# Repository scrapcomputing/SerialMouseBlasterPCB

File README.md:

# Serial Mouse Blaster (a.k.a. Passive USB to Serial Mouse Adapter)

A PCB used for modding a modern optical USB mouse and converting it into a Serial mouse.

This is based on a Raspberry Pi Pico running the SerialMouseBlaster [firmware](https://github.com/scrapcomputing/SerialMouseBlasterFirmware).

# What does it do

The SerialMouseBlaster has two jobs:
- It extracts as much current as possible from the serial port pins and provides power to a Raspberry Pi Pico running the specifically designed low-power firmware, and to a USB optical mouse with the LED resistor mod for low power consumption.
- It does the necessary level shifting that allows the Pico's GPIOs to talk to the serial port pins that are used by the serial mouse protocol.

The end result is an adapter board that converts a USB optical mouse to a serial one with no external power.

# Which mouse can I use?

Short answer: You have to measure it first, but a relatively modern mouse with a < 5mA consumption on idle should work after the resistor mod.

The serial port provides very little power, up to 15mA in total at 5V.
Currently the Pico consumes about half of it and the rest of the circuitry about another 15-20%. So the we only have about 5mA to spare for the USB mouse. So a good mouse candidate is one that consumes up to 5mA.

The problem though is that most USB optical mice consume much more than this.
But most of the power is usually consumed by the LED (usually red) which illuminates the surface.
Luckily the mouse camera can still work even with a much dimmer LED.
So we can reduce the power consumption by adding a resistor in series with the LED.
A good resistor values is usually around 1K Ohms.
Some mice may even work with higher resistor values, but beyond some value the camera can no longer see the surface and the mouse will not register mouse movement.
So for best results use the largest resistor value you can without affecting the functionality of the mouse.

Some mice already have an SMD resistor in-series with the LED (see image below of the Microsoft Basic Optical Mouse v2.0).
This resistor is usually a very low value.
For a cleaner mod, you can simply replace this resistor with another SMD one of much higher value.

You can usually tell if a mouse is low-power enough by simply measuring its idle current, without the resistor mod.
If it is under 5mA, then it has a good chance of working well with a mod.
If not, then the chances are that it will consume too much power even with the mod.

Please note that a typical optical USB mouse will consume several times higher power when you move it as the LED becomes a lot brighter than when it is not moving.

## List of mice that work:
 Brand     |  Model                  | Idle Current | Max Current | Mod Resistor |Modded Idle | Modded Max
-----------|-------------------------|--------------|-------------|--------------|------------|-----------
Microsoft  |Basic Optical Mouse v2.0 | 3.5mA        | ~15mA       |  2.2K        | 2.7mA      | 5.4mA
Logitech   | B100                    | 8.4mA        | ~24mA       |  1K          | 6.4mA      | 8.6mA

## List of mice that consume too much power (mostly very early optical mice):
 Brand     |  Model                   | Idle Current | Max Current |
-----------|--------------------------|--------------|-------------|
Dell       | M-UVDEL1                 | 20.7mA       | 59.2mA      |
Apple      | A1152                    | 26.7mA       | 69.7mA      |
Microsoft  | Basic Optical Mouse      | 29.4mA       | 54.3mA      |
Microsoft  | Wheel Mouse Optical 1.1A | 44.1mA       | 61.4mA      |

> **Note**
> Please help me populate these tables. Feel free to reach out or send out a pull request if you measured your mouse and you want to share your numbers.

# How does it work

The serial port does not provide power.
So any device connected to it either needs to be powered externally, or try to use power from the logic output pins. There are 3 output pins: TXD, DTR and RTS. These can usually provide up to about 5mA at 5V.

The SerialMouseBlaster uses power from all three pins. When the mouse driver initializes the serial port, DTR and RTS are high (about +10V), while TXD is low (about -10V). In order to get power from TXD, it uses a 7555 timer chip as a voltage doubler, which outputs positive voltage.

Level-shifting is done with an LM385 Op Amp which consumes only 1.5mA, as opposed to using a MAX3232, which according to my measurements consumed more than 5mA.

# Serial port pinout

Pin | Name | Direction | Description
----|------|-----------|------------
  1 | CD   | IN        | Carrier Detect
  2 | RXD  | IN        | Receive Data
  3 | TXD  | OUT       | Transmit Data
  4 | DTR  | OUT       | Data Terminal Ready
  5 | GND  |           | Ground
  6 | DSR  | IN        | Data Set Ready
  7 | RTS  | OUT       | Request To Send
  8 | CTS  | IN        | Clear To Send
  9 | IR   | IN        | Ring Indicator

```
Female connector looking at the holes:
 -----------------------
|     -------------     |
|     \ 5 4 3 2 1 /     |
| ( )  \ 9 8 7 6 /  ( ) |
|        -------        |
 -----------------------
```

# Videos
- For a discussion/explanation of the circuit: https://www.youtube.com/watch?v=cGvVPzlRPjM
- Assembly video rev0.1: https://www.youtube.com/watch?v=YjD63UplQ3c

# Bill of materials

Gerber files are published in the releases: https://github.com/scrapcomputing/SerialMouseBlasterPCB/releases

The firmware is available here: https://github.com/scrapcomputing/SerialMouseBlasterFirmware

Reference| Quantity| Value| Footprint | Details
---------|---------|------|-----------|--------
C1 C7 |2|1uF|Capacitor SMD|C 1206 3216Metric Pad1.33x1.80mm
C2 |1|10nF|Capacitor SMD|C 1206 3216Metric Pad1.33x1.80mm
C3 C4 C6 C8 |4|10uF|Capacitor SMD|C 1206 3216Metric Pad1.33x1.80mm
D11 |1|BZX84-C5V1|Diode SMD|D SOT-23 ANK
D1 D2 D3 D4 D5 D6 |6|BAS40-04|Package TO SOT SMD|SOT-23
J1 |1|Conn 01x05|Connector PinHeader 2.54mm|PinHeader 1x05 P2.54mm Vertical
J2 |1|Conn 01x04 Male|Connector PinHeader 2.54mm|PinHeader 1x04 P2.54mm Vertical
J3 |1|Conn 01x03 Male|Connector PinHeader 2.54mm|PinHeader 1x03 P2.54mm Vertical
Q1 |1|MMBTA92|Package TO SOT SMD|SOT-23
R1 R3 R4 R8 |4|1K|Resistor SMD|R 1206 3216Metric Pad1.30x1.75mm
R2 R5 R6 R7 |4|22K|Resistor SMD|R 1206 3216Metric Pad1.30x1.75mm
U1 |1|ICM7555xP|Package SO|SO-8 5.3x6.2mm P1.27mm
U2 |1|LM358|Package SO|SO-8 5.3x6.2mm P1.27mm
U3 |1|RaspberryPi Pico| N/A | Raspberry Pi Pico

# Changelist
- Rev0.4 : Handles Tx with positive voltage, adds protection diode for 555.
- Rev0.3 : First SMD only revision.
- Rev0.2 : Initial release. Fixes minor issues of Rev0.1.
- Rev0.1 : Initial revision (not released)

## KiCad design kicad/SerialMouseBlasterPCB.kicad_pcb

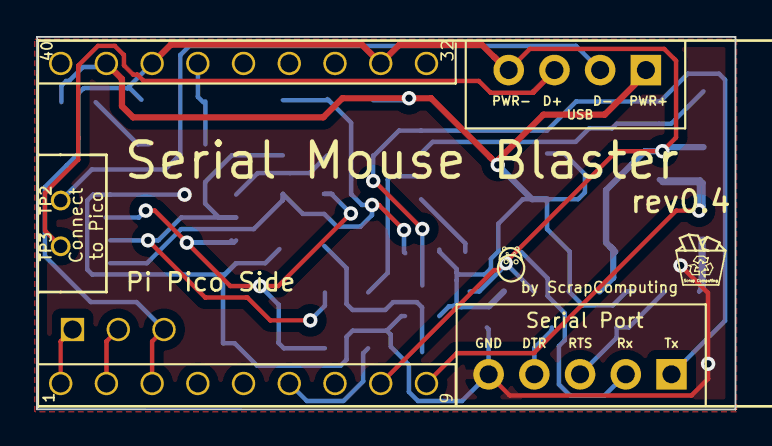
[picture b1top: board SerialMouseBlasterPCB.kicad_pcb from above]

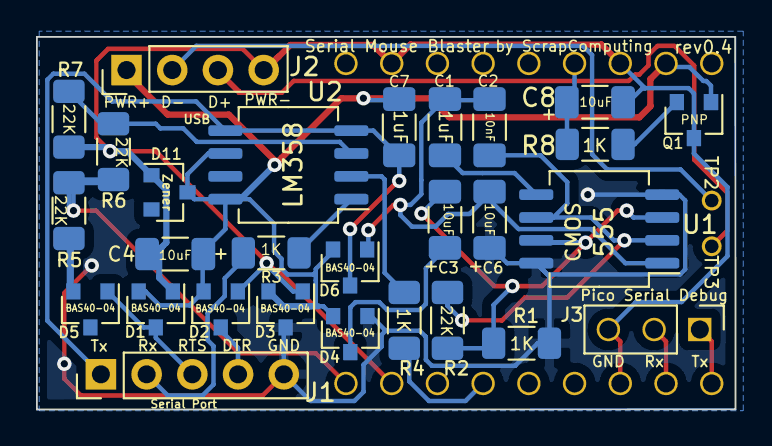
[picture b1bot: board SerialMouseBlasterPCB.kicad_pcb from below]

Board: 2 copper layers, 38.8 x 20.7 mm, 29 parts (28 on the bottom side), 24 nets.

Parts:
C1, C7: 1uF; C_1206_3216Metric_Pad1.33x1.80mm_HandSolder
C2: 10nF; C_1206_3216Metric_Pad1.33x1.80mm_HandSolder
C3, C4, C6, C8: 10uF; C_1206_3216Metric_Pad1.33x1.80mm_HandSolder
D1, D2, D3, D4, D5, D6: BAS40-04; SOT-23
D11: BZX84-C5V1; D_SOT-23_ANK
J1: Conn_01x05; PinHeader_1x05_P2.54mm_Vertical
J2: Conn_01x04_Male; PinHeader_1x04_P2.54mm_Vertical
J3: Conn_01x03_Male; PinHeader_1x03_P2.54mm_Vertical
Q1: MMBTA92; SOT-23
R1, R3, R4, R8: 1K; R_1206_3216Metric_Pad1.30x1.75mm_HandSolder
R2, R5, R6, R7: 22K; R_1206_3216Metric_Pad1.30x1.75mm_HandSolder
U1: ICM7555xP; SO-8_5.3x6.2mm_P1.27mm
U2: LM358; SO-8_5.3x6.2mm_P1.27mm
U3: RaspberryPi_Pico; raspberry_pi_pico

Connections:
/D+: J2.3, U3.42
/D-: J2.2, U3.41
/DTR: D2.3, J1.4
/GND: C6.1, D3.3, D4.1, J1.5, R1.1, U1.4, U1.8
/PWR+: C4.1, C7.1, D1.2, D2.2, D3.2, D4.2, D6.2, D11.1, J2.1, Q1.1, U2.6, U2.8, U3.39
/PWR-: C4.2, C8.2, D1.1, D2.1, D3.1, D11.2, J2.4, J3.3, Q1.3, R7.2, U3.3, U3.8, U3.33, U3.38
/PicoRx: J3.2, U3.2
/PicoTx: J3.1, U3.1
/RTS: D1.3, D5.1, J1.3
/RTS_: R5.2, R6.1, U3.9
/RX: J1.2, R3.2
/RxIN: R4.1, U3.6
/TX: C7.2, D6.3, J1.1, U2.4, U2.5
unnamed: C1.1, U1.5
unnamed: C1.2, C2.2, C6.2, D6.1, U1.1
unnamed: C2.1, R2.1, U1.2, U1.6
unnamed: C3.1, D4.3
unnamed: C3.2, R1.2, R2.2, U1.3, U1.7
unnamed: C8.1, R8.1, U3.37
unnamed: D5.2, R5.1
unnamed: Q1.2, R8.2
unnamed: R3.1, U2.1
unnamed: R4.2, U2.2
unnamed: R6.2, R7.1, U2.3

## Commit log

2023-06-18 Rev0.2
2023-06-18 Add link to PCB video
2023-06-18 Improves Readme. Adds mouse power consumption tables.
2023-06-19 Rev 0.3: All components are SMD and the board is much smaller
    - Footprint is much smaller and the gap between the Pico and the PCB can be minimal
    - All SMD components are on one side of the board, which makes them accessible even when the Pico is soldered on
    - Capacitor values have been reduced
    - Pico reset is now fixed with the use of a PNP bleeder transistor
    - All component values are now printed on the PCB
2023-07-08 Rev 0.4: Support positive Tx and add protection diode for 555.
    This also changes some resistor and capacitor values to make it easier to assemble.
